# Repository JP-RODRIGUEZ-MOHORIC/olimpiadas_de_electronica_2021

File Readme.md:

## _Olimpiadas de electronica 2021_

Este es un proyecto institucional realizado por los alumnos de la EEST N°5 de Temperley para las olimpiadas de electronica de 2021.
Integrantes:

- Alejo Perin
- Juan Pablo Rodriguez Mohoric
- Ivan Seifert
- Ramiro Sanchez
- Agustin Di Santo

## Proyecto 

El proyecto consta de un sistema de detección de CO2 para una habitación. Cuando se detecte un alto nivel del mismo se activará un mecanismo de ventilación para la extracción de este. El nivel de CO2 y otros datos podran ser vizualizados mediante una página web a la cual se ingresará con una contraseña a través de un teclado matricial para poder descargar un reporte de niveles de CO2 en función del tiempo.

## Tecnologias utilizadas

- C++ (Arduino)
- HTML
- CSS

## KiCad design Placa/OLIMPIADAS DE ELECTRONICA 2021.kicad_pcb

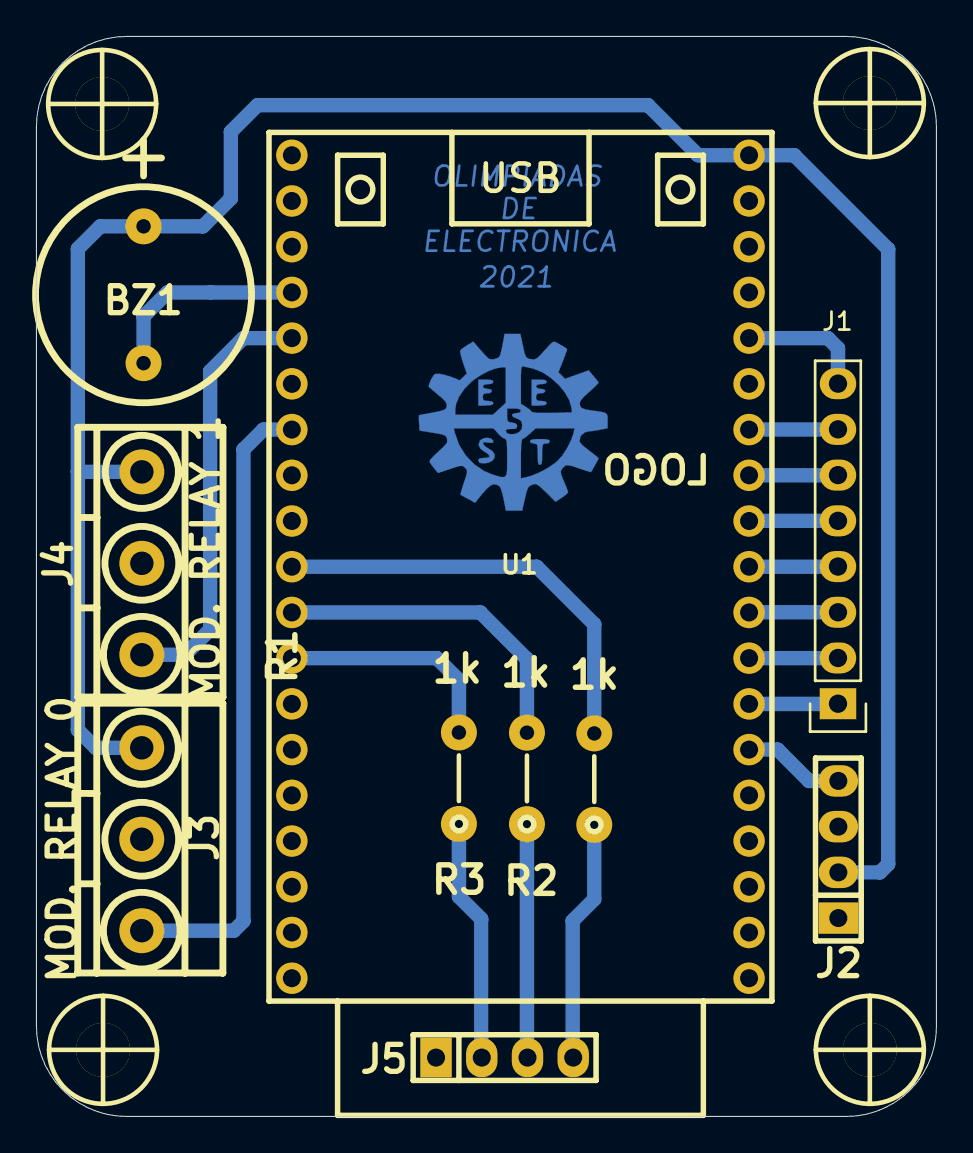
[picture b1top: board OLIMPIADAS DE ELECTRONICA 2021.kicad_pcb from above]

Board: 2 copper layers, 50.0 x 60.0 mm, 14 parts (0 on the bottom side), 20 nets.

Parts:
BZ1: BUZZER; Buzzer_12mm
H1, H2, H3, H4: Mounting_Hole; hole_3mm
J1: TECLADO MATRICIAL; Pin_Header_Straight_1x08
J2: SENSOR CO2; pin_strip_4
J3: MOD. RELAY 0; BORNERA3_AZUL
J4: MOD. RELAY 1; BORNERA3_AZUL
J5: LED RGB; pin_strip_4
R1, R2, R3: 1k; RES0.2
U1: ESP32_DEVKITC

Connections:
/5V: BZ1.1, J2.2, J3.1, J4.1, U1.19
/GND: J2.1, J3.2, J4.2, J5.1, U1.32, U1.38
/PIN_2: J4.3, U1.24
/PIN_4: J3.3, U1.26
/PIN_5: R1.2, U1.29
/PIN_12: J1.7, U1.13
/PIN_13: J1.8, U1.15
/PIN_14: J1.6, U1.12
/PIN_15: BZ1.2, U1.23
/PIN_18: R2.2, U1.30
/PIN_19: R3.2, U1.31
/PIN_25: J1.3, U1.9
/PIN_26: J1.4, U1.10
/PIN_27: J1.5, U1.11
/PIN_32: J1.1, U1.7
/PIN_33: J1.2, U1.8
/PIN_35: J2.4, U1.6
unnamed: J5.2, R3.1
unnamed: J5.3, R2.1
unnamed: J5.4, R1.1

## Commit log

2021-09-28 ventilacion changed to a boolean variable
2021-09-29 Create Readme.md
    Se incluye un archivo Readme
2021-09-29 rules added
2021-09-29 new variable CO2_LIMITE added
2021-10-03 Esp32 code added
2021-10-03 Ip String added and ventilation status
2021-10-03 IP string fixed
2021-10-04 sensor pin changed to 35
2021-10-04 table users session data and real time refresh
2021-10-04 language changed and new functions added
2021-10-04 table data changed and rtc function added
2021-10-04 download table function added
2021-10-04 comments language changed
2021-10-12 Scheme and PCB files added
